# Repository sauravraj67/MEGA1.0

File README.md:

# MEGA1.0

I am making a cool micro pad for myself it has 8 key switches, one rotor encoder and a 0.91 inch screen. It is based on XIAO RP2040. It has 3 layers which would be controlled by the rotor encoder and the selected layer would be displayed on the screen. I also used Hot-Swap so that i don't have to solder/de-solder the switches while changing it.
## Features

- Based on Xiao Rp2040
- Has HotSnap base
## Firmware
- Firmware is based on QMK.

- ### Schematic<br><br>

###  PCB Design<br><br>

### 3D Design <br><br>

# Bill of Materials (BOM)

## Components

| Qty | Part Description | Link | Cost (USD) |
|-----|------------------|------|-------------|
| 1(pack of 10) + shipping | Kailh Hot-Swap Switch Sockets + shipping | 	https://neomacro.in/products/kailh-mx-hotswap-socket?variant=49467139227926 | 2.33 |
| 1 | PCB Fabrication + 3D Print + Shipping | https://jlcpcb.com | 9.65 |

## Final Total: **$11.99 USD**

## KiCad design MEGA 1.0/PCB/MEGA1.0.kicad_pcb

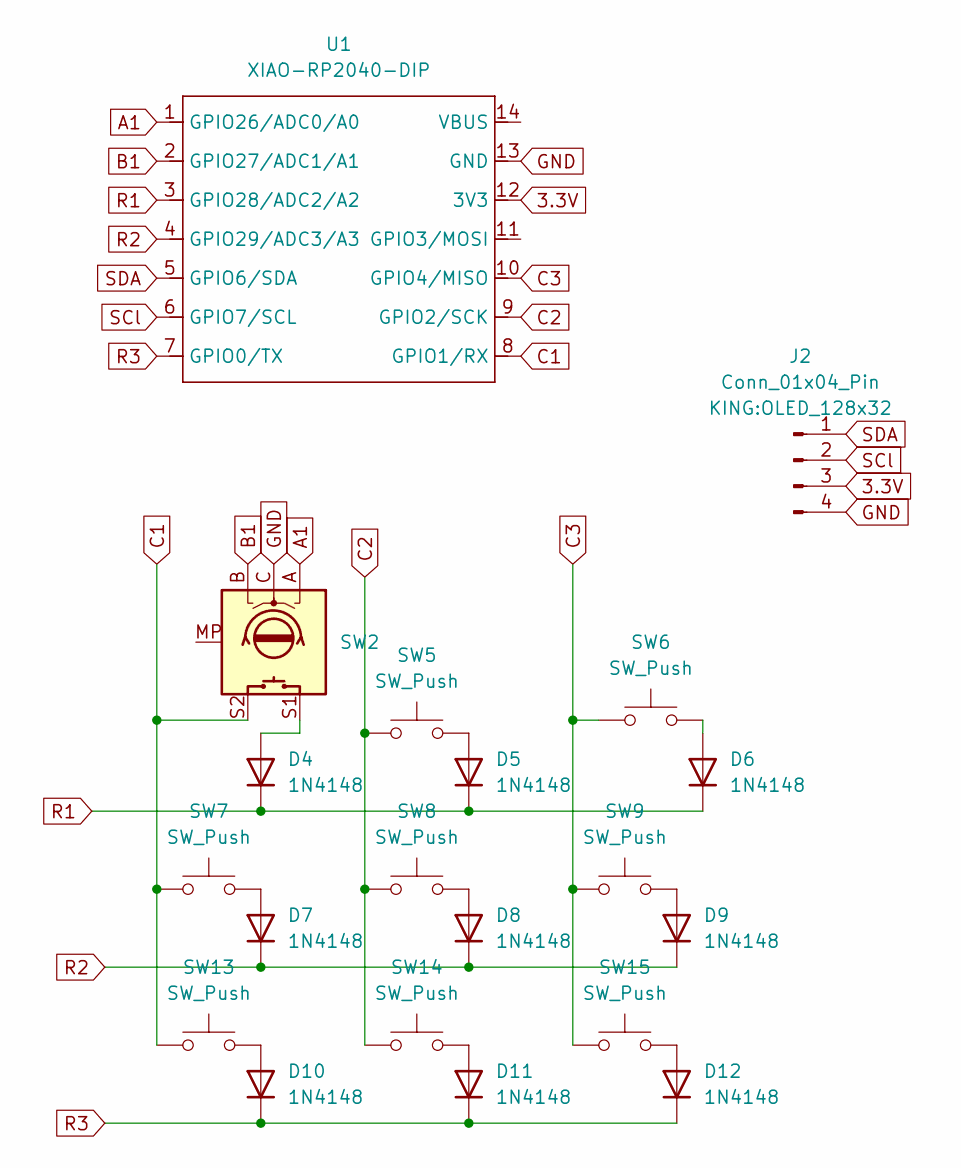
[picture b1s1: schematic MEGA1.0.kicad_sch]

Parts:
D4, D5, D6, D7, D8, D9, D10, D11, D12: 1N4148; D_DO-35_SOD27_P7.62mm_Horizontal
J2: Conn_01x04_Pin; OLED_128x32
SW2: RotaryEncoder_Switch_MP; RotaryEncoder_Alps_EC11E-Switch_Vertical_H20mm
SW5, SW6, SW7, SW8, SW9, SW13, SW14, SW15: SW_Push; MX100H
U1: XIAO-RP2040-DIP

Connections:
3.3V: J2.3, U1.12 (3V3)
A1: SW2.A, U1.1 (GPIO26/ADC0/A0)
B1: SW2.B, U1.2 (GPIO27/ADC1/A1)
C1: SW2.S2, SW7.1, SW13.1, U1.8 (GPIO1/RX)
C2: SW5.1, SW8.1, SW14.1, U1.9 (GPIO2/SCK)
C3: SW6.1, SW9.1, SW15.1, U1.10 (GPIO4/MISO)
GND: J2.4, SW2.C, U1.13 (GND)
unnamed: D4.2 (A), SW2.S1
unnamed: D5.2 (A), SW5.2
unnamed: D6.2 (A), SW6.2
unnamed: D7.2 (A), SW7.2
unnamed: D8.2 (A), SW8.2
unnamed: D9.2 (A), SW9.2
unnamed: D10.2 (A), SW13.2
unnamed: D11.2 (A), SW14.2
unnamed: D12.2 (A), SW15.2
R1: D4.1 (K), D5.1 (K), D6.1 (K), U1.3 (GPIO28/ADC2/A2)
R2: D7.1 (K), D8.1 (K), D9.1 (K), U1.4 (GPIO29/ADC3/A3)
R3: D10.1 (K), D11.1 (K), D12.1 (K), U1.7 (GPIO0/TX)
SCl: J2.2, U1.6 (GPIO7/SCL)
SDA: J2.1, U1.5 (GPIO6/SDA)

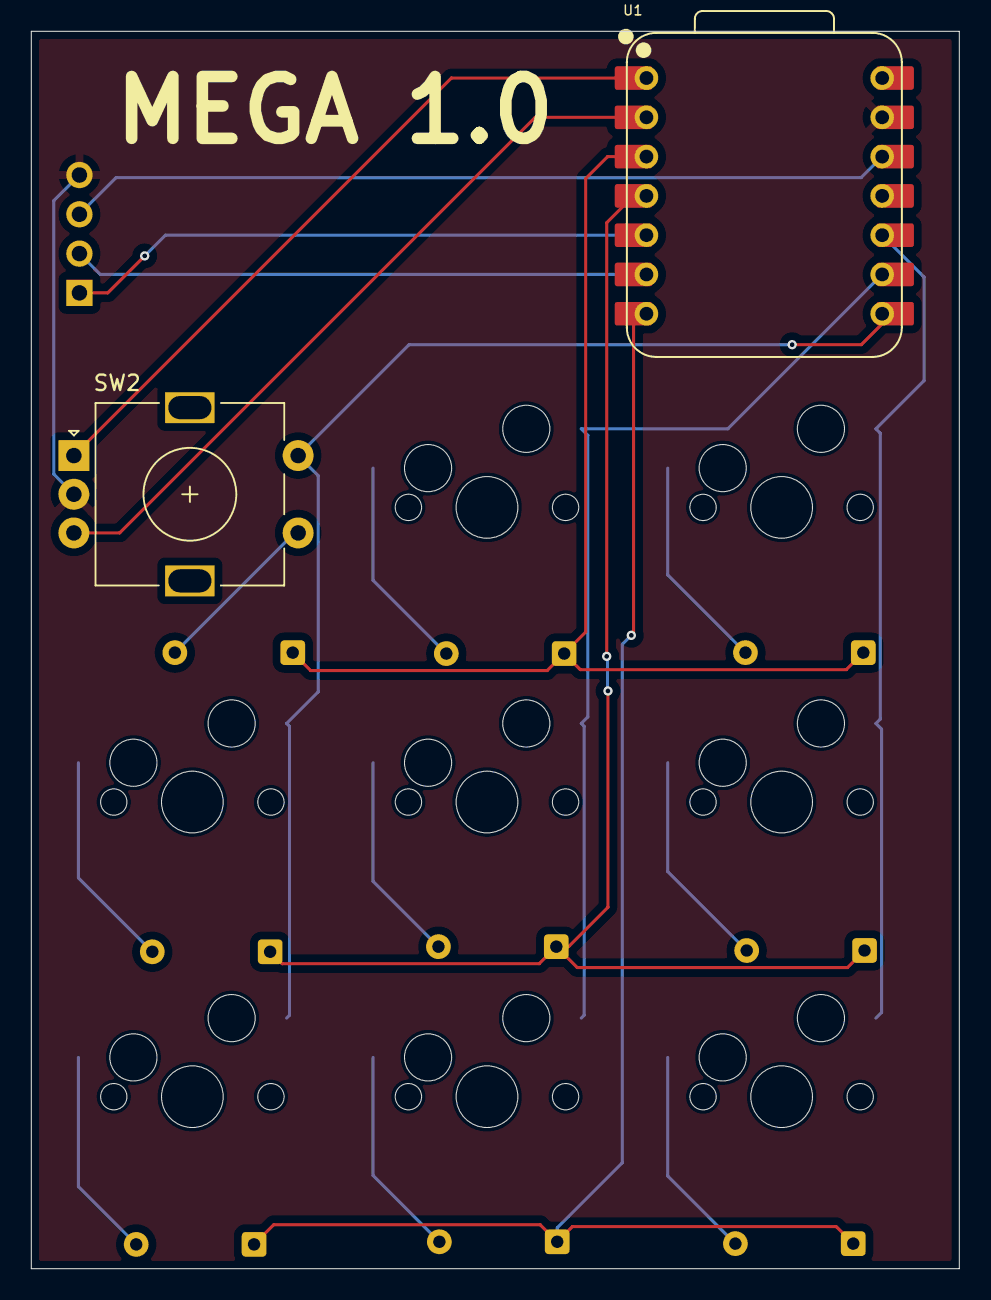
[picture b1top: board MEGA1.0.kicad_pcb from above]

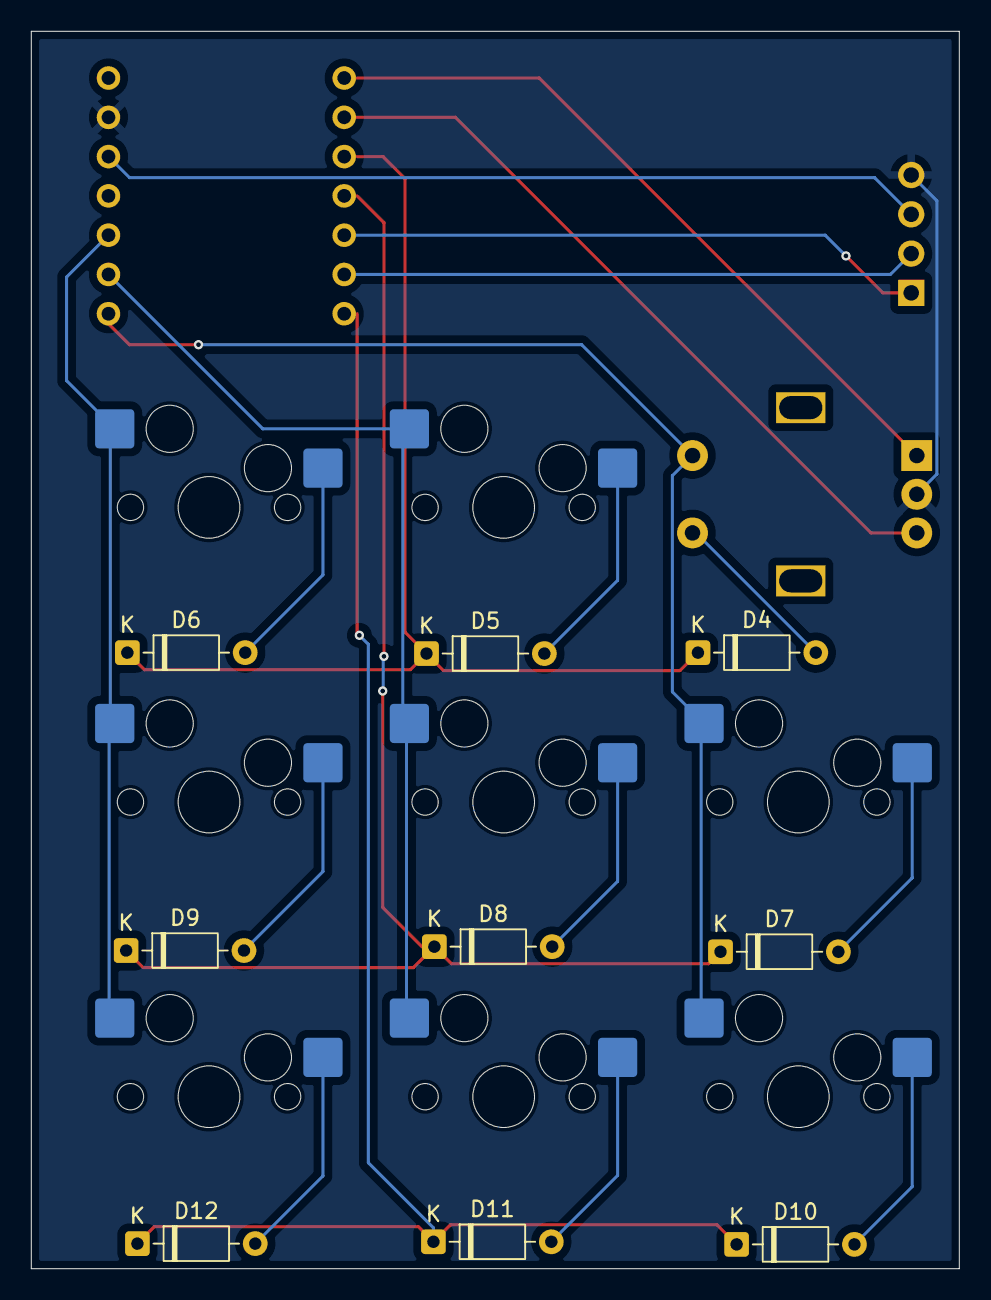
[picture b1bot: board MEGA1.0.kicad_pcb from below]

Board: 2 copper layers, 60.0 x 80.0 mm, 20 parts (17 on the bottom side), 21 nets.
